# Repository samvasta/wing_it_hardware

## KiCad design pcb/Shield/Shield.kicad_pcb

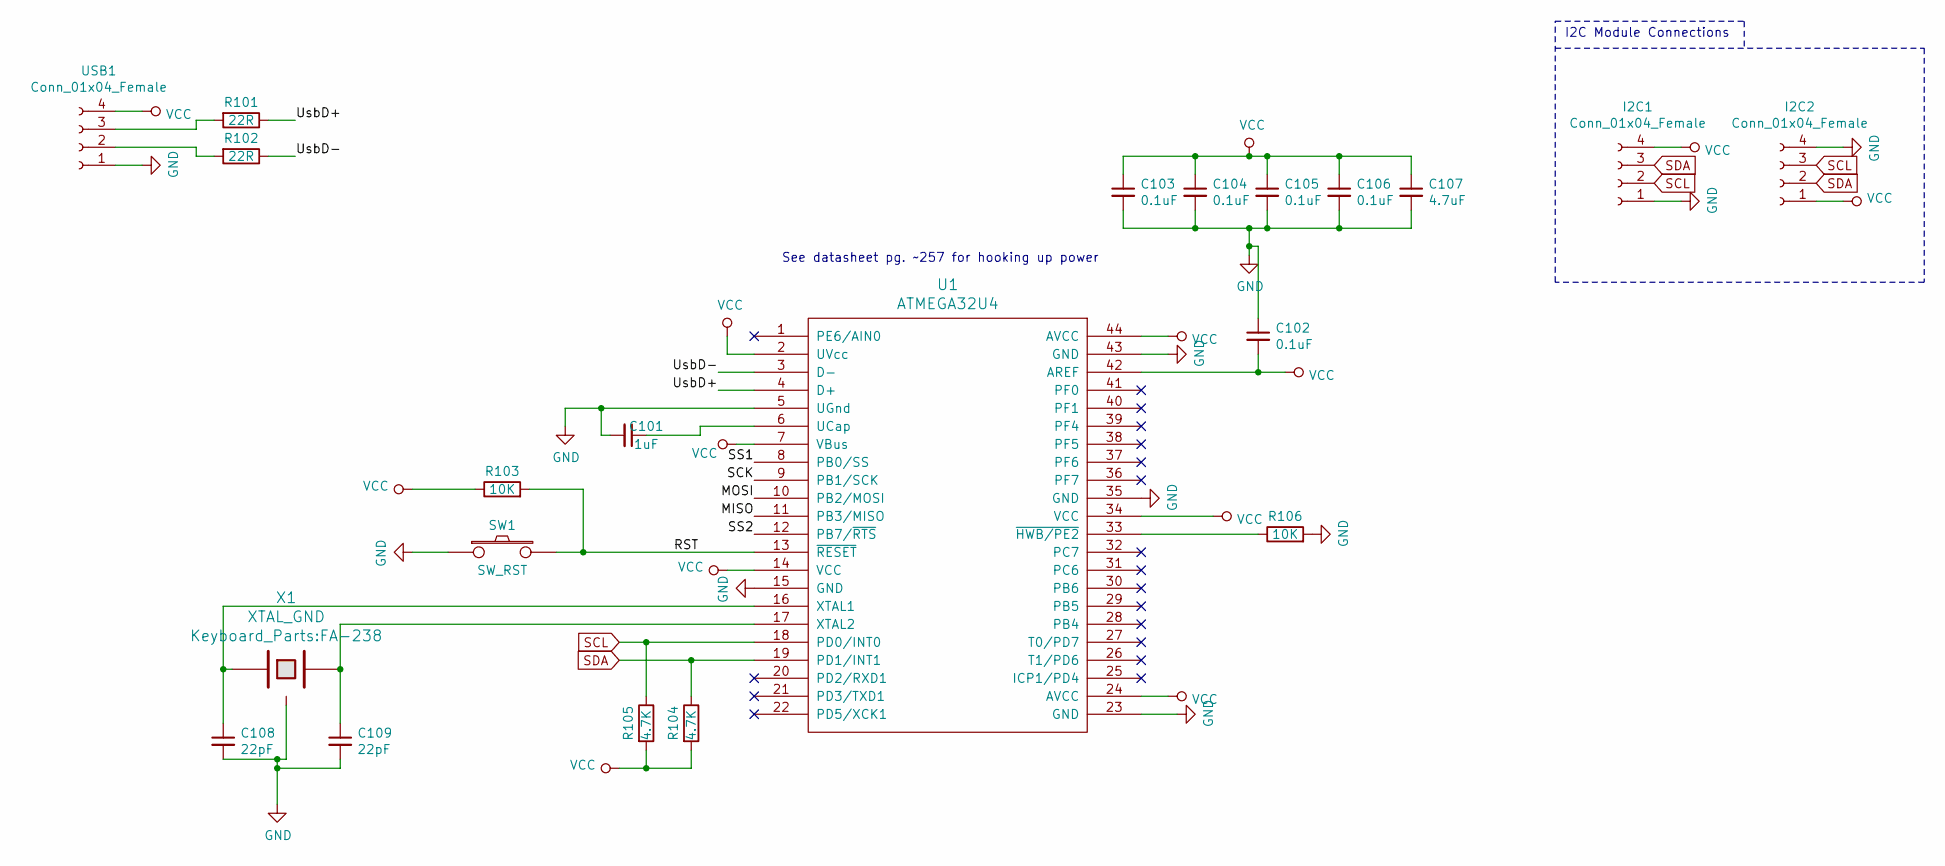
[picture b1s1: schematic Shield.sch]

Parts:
C101: 1uF; C_0805_2012Metric_Pad1.15x1.40mm_HandSolder
C102, C103, C104, C105, C106: 0.1uF; C_0805_2012Metric_Pad1.15x1.40mm_HandSolder
C107: 4.7uF; C_0805_2012Metric_Pad1.15x1.40mm_HandSolder
C108, C109: 22pF; C_0805_2012Metric_Pad1.15x1.40mm_HandSolder
I2C1, I2C2: Conn_01x04_Female; Terminal_Block_4pos_On_Shore_Tech.
R101, R102: 22R; R_0805_2012Metric_Pad1.15x1.40mm_HandSolder
R103, R106: 10K; R_0805_2012Metric_Pad1.15x1.40mm_HandSolder
R104, R105: 4.7K; R_0805_2012Metric_Pad1.15x1.40mm_HandSolder
SW1: SW_RST; MomentarySwitch_B3U-1000P
U1: ATMEGA32U4; ATMEGA32U4-AU_FixedMask
USB1: Conn_01x04_Female; Terminal_Block_4pos_On_Shore_Tech.
X1: XTAL_GND; FA-238

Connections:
/MISO: U1.11 (PB3/MISO)
/MOSI: U1.10 (PB2/MOSI)
/RST: R103.2, SW1.2, U1.13 (~RESET)
/SCK: U1.9 (PB1/SCK)
/SS1: U1.8 (PB0/SS)
/SS2: U1.12 (PB7/~RTS)
/UsbD+: R101.1, U1.4 (D+)
/UsbD-: R102.1, U1.3 (D-)
GND: C101.2, C102.1, C103.2, C104.2, C105.2, C106.2, C107.2, C108.2, C109.2, I2C1.1, I2C2.4, R106.2, SW1.1, U1.5 (UGnd), U1.15 (GND), U1.23 (GND), U1.35 (GND), U1.43 (GND), USB1.1, X1.3
unnamed: C101.1, U1.6 (UCap)
unnamed: C108.1, U1.16 (XTAL1), X1.1
unnamed: C109.1, U1.17 (XTAL2), X1.2
unnamed: R101.2, USB1.3
unnamed: R102.2, USB1.2
unnamed: R106.1, U1.33 (~HWB/PE2)
SCL: I2C1.2, I2C2.3, R105.1, U1.18 (PD0/INT0)
SDA: I2C1.3, I2C2.2, R104.1, U1.19 (PD1/INT1)
VCC: C102.2, C103.1, C104.1, C105.1, C106.1, C107.1, I2C1.4, I2C2.1, R103.1, R104.2, R105.2, U1.2 (UVcc), U1.7 (VBus), U1.14 (VCC), U1.24 (AVCC), U1.34 (VCC), U1.42 (AREF), U1.44 (AVCC), USB1.4

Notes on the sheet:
See datasheet pg. ~~257 for hooking up power
I2C Module Connections

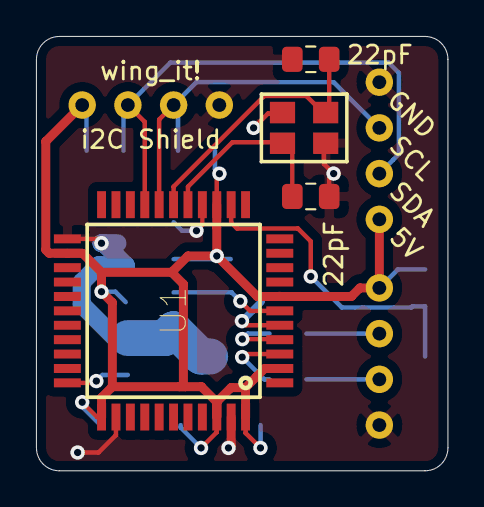
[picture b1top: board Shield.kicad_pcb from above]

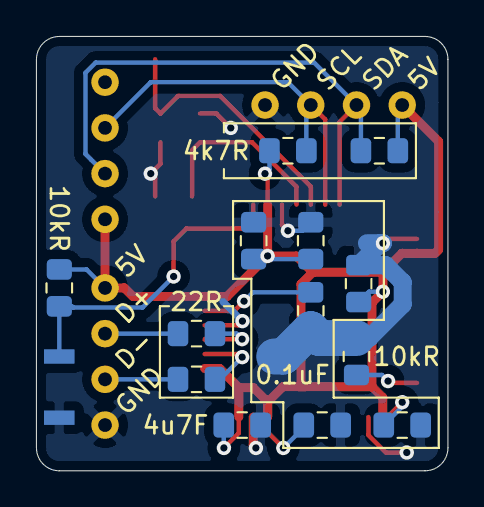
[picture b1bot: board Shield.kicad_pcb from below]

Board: 2 copper layers, 22.9 x 24.1 mm, 21 parts (15 on the bottom side), 13 nets.

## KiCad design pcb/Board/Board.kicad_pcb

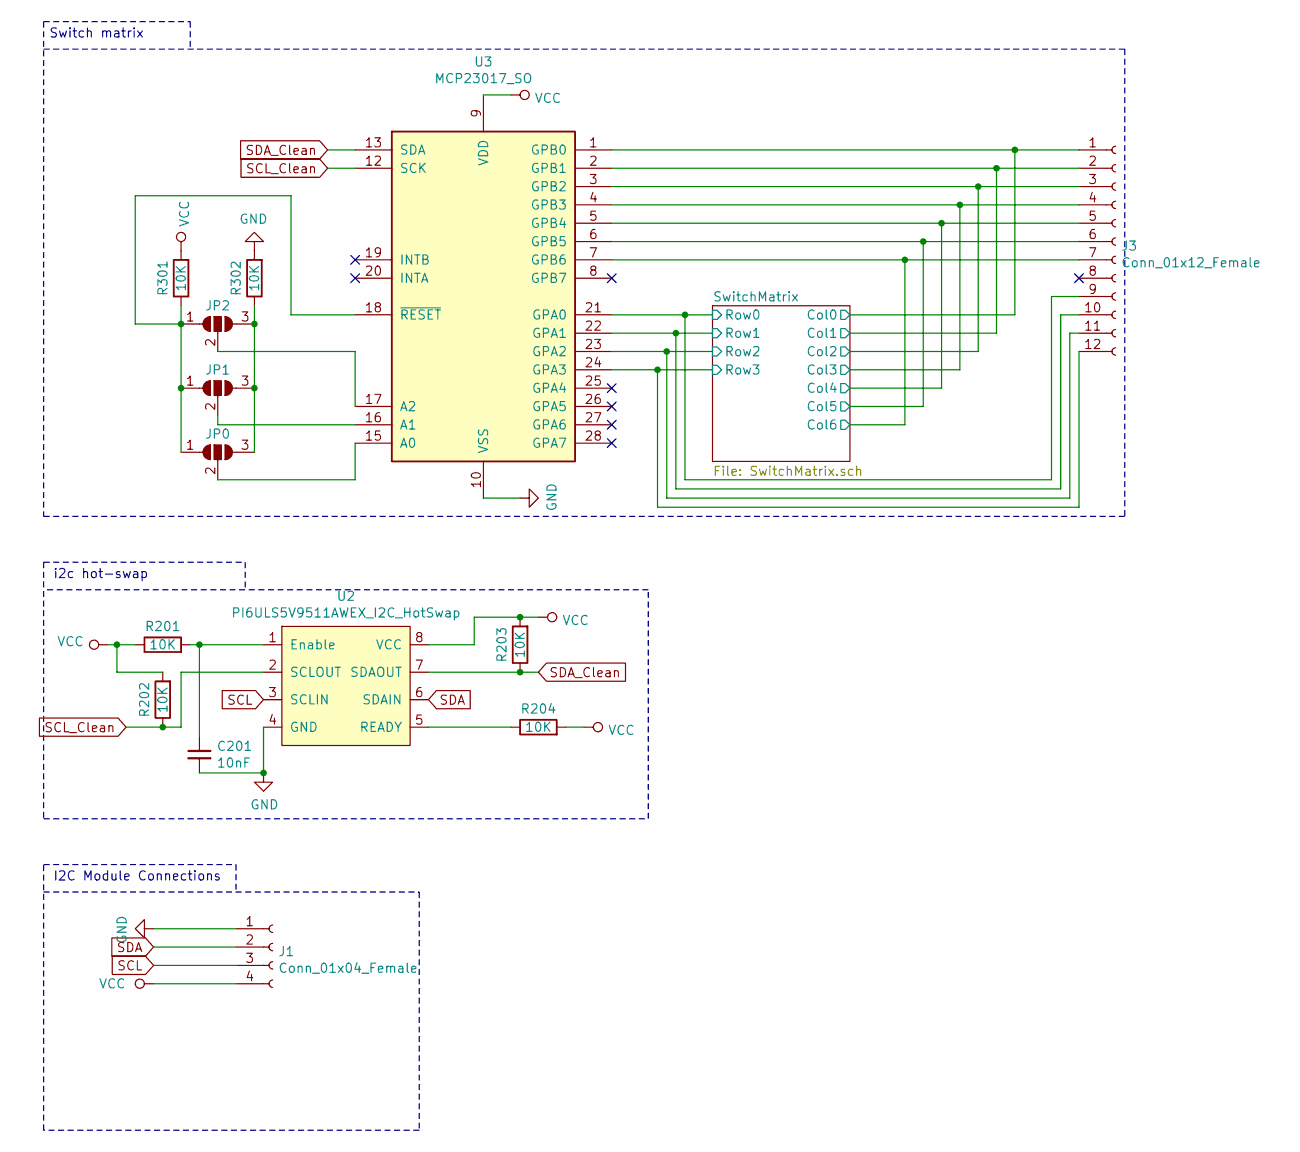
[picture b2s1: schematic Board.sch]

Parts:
C201: 10nF; C_0805_2012Metric_Pad1.15x1.40mm_HandSolder
J1: Conn_01x04_Female; PinHeader_1x04_P2.54mm_Vertical
J3: Conn_01x12_Female; PinHeader_1x12_P2.54mm_Vertical
JP0, JP1, JP2: SolderJumper_3_Open; SolderJumper-3_P1.3mm_Open_RoundedPad1.0x1.5mm
R201, R202, R203, R204, R301, R302: 10K; R_0805_2012Metric_Pad1.15x1.40mm_HandSolder
U2: PI6ULS5V9511AWEX_I2C_HotSwap; PI6ULS5V9511A_I2C_HotSwap
U3: MCP23017_SO; SSOP-28_5.3x10.2mm_P0.65mm

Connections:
/SwitchMatrix/Col0: J3.1, U3.1 (GPB0); also elsewhere on the board
/SwitchMatrix/Col1: J3.2, U3.2 (GPB1); also elsewhere on the board
/SwitchMatrix/Col2: J3.3, U3.3 (GPB2); also elsewhere on the board
/SwitchMatrix/Col3: J3.4, U3.4 (GPB3); also elsewhere on the board
/SwitchMatrix/Col4: J3.5, U3.5 (GPB4); also elsewhere on the board
/SwitchMatrix/Col5: J3.6, U3.6 (GPB5); also elsewhere on the board
/SwitchMatrix/Col6: J3.7, U3.7 (GPB6); also elsewhere on the board
/SwitchMatrix/Row0: J3.9, U3.21 (GPA0); also elsewhere on the board
/SwitchMatrix/Row1: J3.10, U3.22 (GPA1); also elsewhere on the board
/SwitchMatrix/Row2: J3.11, U3.23 (GPA2); also elsewhere on the board
/SwitchMatrix/Row3: J3.12, U3.24 (GPA3); also elsewhere on the board
GND: C201.2, J1.1, R302.2, U2.4 (GND), U3.10 (VSS); also elsewhere on the board
unnamed: C201.1, R201.2, U2.1 (Enable)
unnamed 40: JP0.1 (A), JP1.1 (A), JP2.1 (A), R301.1, U3.18 (~RESET~); also elsewhere on the board
unnamed 41: JP0.2 (C), U3.15 (A0); also elsewhere on the board
unnamed 42: JP0.3 (B), JP1.3 (B), JP2.3 (B), R302.1; also elsewhere on the board
unnamed 43: JP1.2 (C), U3.16 (A1); also elsewhere on the board
unnamed 44: JP2.2 (C), U3.17 (A2); also elsewhere on the board
unnamed: R204.1, U2.5 (READY)
unnamed 46: U3.8 (GPB7); also elsewhere on the board
unnamed 47: U3.11 (NC); also elsewhere on the board
unnamed 48: U3.14 (NC); also elsewhere on the board
unnamed 49: U3.19 (INTB); also elsewhere on the board
unnamed 50: U3.20 (INTA); also elsewhere on the board
unnamed 51: U3.25 (GPA4); also elsewhere on the board
unnamed 52: U3.26 (GPA5); also elsewhere on the board
unnamed 53: U3.27 (GPA6); also elsewhere on the board
unnamed 54: U3.28 (GPA7); also elsewhere on the board
SCL: J1.3, U2.3 (SCLIN)
SCL_Clean: R202.1, U2.2 (SCLOUT), U3.12 (SCK); also elsewhere on the board
SDA: J1.2, U2.6 (SDAIN)
SDA_Clean: R203.1, U2.7 (SDAOUT), U3.13 (SDA); also elsewhere on the board
VCC: J1.4, R201.1, R202.2, R203.2, R204.2, R301.2, U2.8 (VCC), U3.9 (VDD); also elsewhere on the board

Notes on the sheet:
Switch matrix
I2C Module Connections
i2c hot-swap

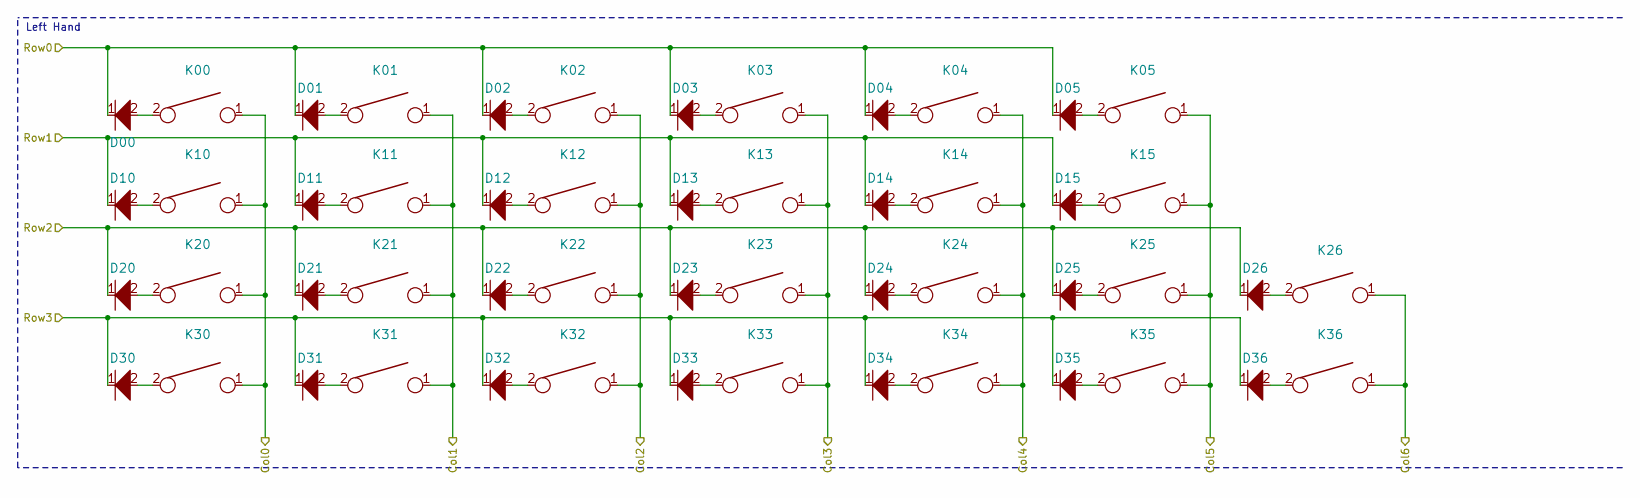
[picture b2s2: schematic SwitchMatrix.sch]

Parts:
D00, D01, D02, D03, D04, D05, D10, D11, D12, D13, D14, D15, D20, D21, D22, D23, D24, D25, D26, D30, D31, D32, D33, D34, D35, D36: D; D_MiniMELF_Handsoldering_Shorter_Pads_DoubleSided
K00, K01, K02, K03, K04, K05, K10, K11, K12, K13, K14, K15, K20, K21, K22, K23, K24, K25, K30, K31, K32, K33, K34, K35: KEYSW; Kailh_socket_reversible
K26, K36: KEYSW; switch_off_board

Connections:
/SwitchMatrix/Col0: K00.1, K10.1, K20.1, K30.1; also elsewhere on the board
/SwitchMatrix/Col1: K01.1, K11.1, K21.1, K31.1; also elsewhere on the board
/SwitchMatrix/Col2: K02.1, K12.1, K22.1, K32.1; also elsewhere on the board
/SwitchMatrix/Col3: K03.1, K13.1, K23.1, K33.1; also elsewhere on the board
/SwitchMatrix/Col4: K04.1, K14.1, K24.1, K34.1; also elsewhere on the board
/SwitchMatrix/Col5: K05.1, K15.1, K25.1, K35.1; also elsewhere on the board
/SwitchMatrix/Col6: K26.1, K36.1; also elsewhere on the board
/SwitchMatrix/Row0: D00.1, D01.1, D02.1, D03.1, D04.1, D05.1; also elsewhere on the board
/SwitchMatrix/Row1: D10.1, D11.1, D12.1, D13.1, D14.1, D15.1; also elsewhere on the board
/SwitchMatrix/Row2: D20.1, D21.1, D22.1, D23.1, D24.1, D25.1, D26.1; also elsewhere on the board
/SwitchMatrix/Row3: D30.1, D31.1, D32.1, D33.1, D34.1, D35.1, D36.1; also elsewhere on the board
unnamed: D00.2, K00.2
unnamed: D01.2, K01.2
unnamed: D02.2, K02.2
unnamed: D03.2, K03.2
unnamed: D04.2, K04.2
unnamed: D05.2, K05.2
unnamed: D10.2, K10.2
unnamed: D11.2, K11.2
unnamed: D12.2, K12.2
unnamed: D13.2, K13.2
unnamed: D14.2, K14.2
unnamed: D15.2, K15.2
unnamed: D20.2, K20.2
unnamed: D21.2, K21.2
unnamed: D22.2, K22.2
unnamed: D23.2, K23.2
unnamed: D24.2, K24.2
unnamed: D25.2, K25.2
unnamed: D26.2, K26.2
unnamed: D30.2, K30.2
unnamed: D31.2, K31.2
unnamed: D32.2, K32.2
unnamed: D33.2, K33.2
unnamed: D34.2, K34.2
unnamed: D35.2, K35.2
unnamed: D36.2, K36.2

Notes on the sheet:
Left Hand

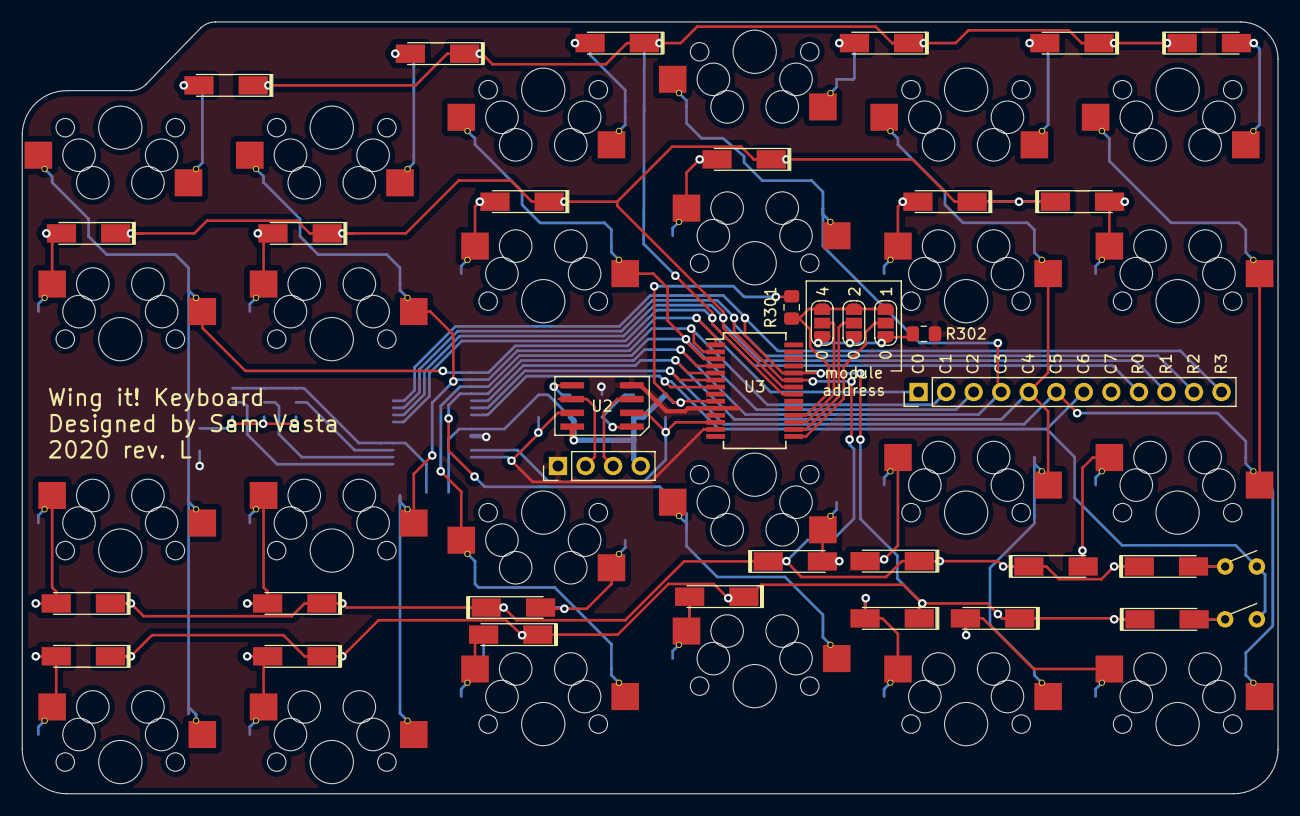
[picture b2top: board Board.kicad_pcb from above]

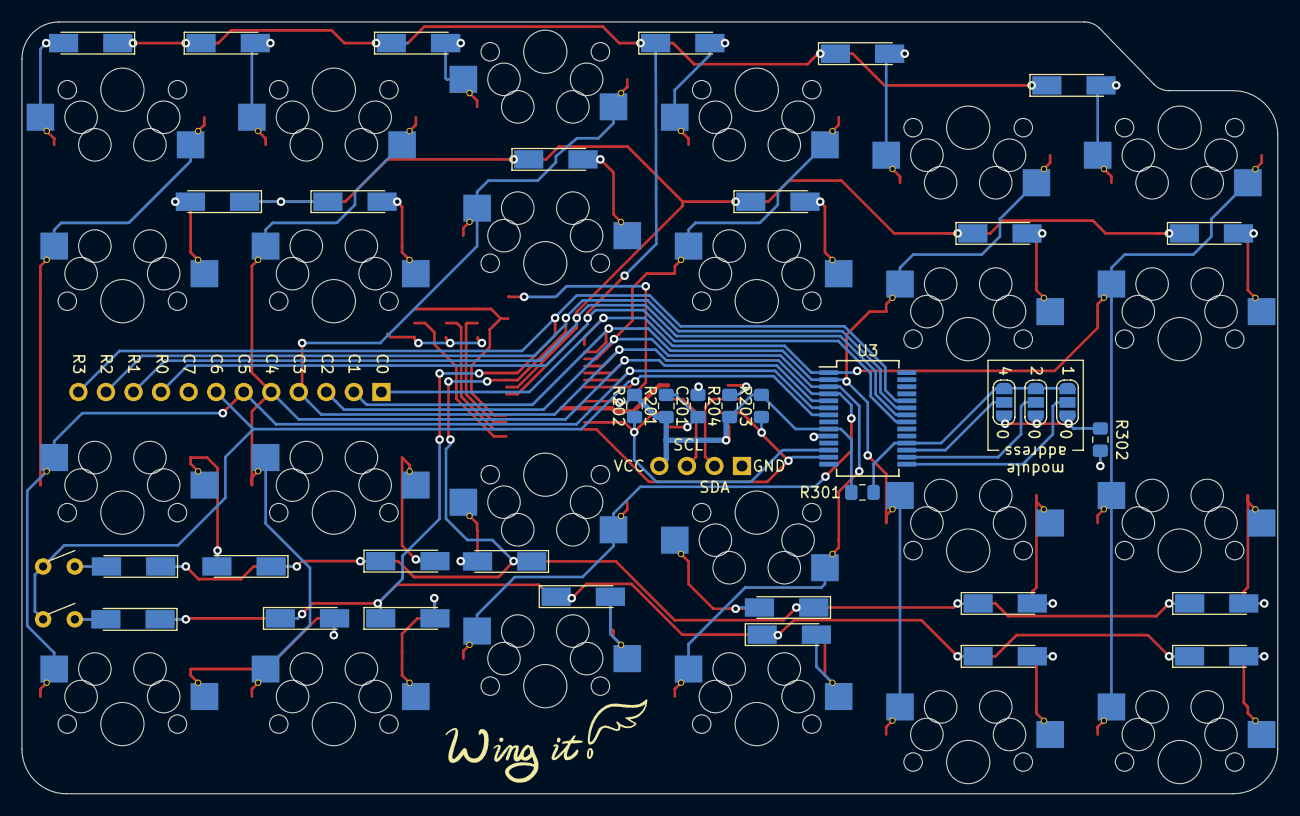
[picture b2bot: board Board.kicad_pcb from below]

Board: 2 copper layers, 115.8 x 71.1 mm, 72 parts (11 on the bottom side), 59 nets.

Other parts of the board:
JP0#2, JP1#2, JP2#2: SolderJumper_3_Open; SolderJumper-3_P1.3mm_Open_RoundedPad1.0x1.5mm
R301#2, R302#2: 10K; R_0805_2012Metric_Pad1.15x1.40mm_HandSolder
U3#2: MCP23017_SO; SSOP-28_5.3x10.2mm_P0.65mm

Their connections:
/SwitchMatrix/Col0: U3#2.1; also elsewhere on the board
/SwitchMatrix/Col1: U3#2.2; also elsewhere on the board
/SwitchMatrix/Col2: U3#2.3; also elsewhere on the board
/SwitchMatrix/Col3: U3#2.4; also elsewhere on the board
/SwitchMatrix/Col4: U3#2.5; also elsewhere on the board
/SwitchMatrix/Col5: U3#2.6; also elsewhere on the board
/SwitchMatrix/Col6: U3#2.7; also elsewhere on the board
/SwitchMatrix/Row0: U3#2.21; also elsewhere on the board
/SwitchMatrix/Row1: U3#2.22; also elsewhere on the board
/SwitchMatrix/Row2: U3#2.23; also elsewhere on the board
/SwitchMatrix/Row3: U3#2.24; also elsewhere on the board
GND: R302#2.2, U3#2.10; also elsewhere on the board
unnamed 40: JP0#2.1, JP1#2.1, JP2#2.1, R301#2.1, U3#2.18; also elsewhere on the board
unnamed 41: JP0#2.2, U3#2.15; also elsewhere on the board
unnamed 42: JP0#2.3, JP1#2.3, JP2#2.3, R302#2.1; also elsewhere on the board
unnamed 43: JP1#2.2, U3#2.16; also elsewhere on the board
unnamed 44: JP2#2.2, U3#2.17; also elsewhere on the board
unnamed 46: U3#2.8; also elsewhere on the board
unnamed 47: U3#2.11; also elsewhere on the board
unnamed 48: U3#2.14; also elsewhere on the board
unnamed 49: U3#2.19; also elsewhere on the board
unnamed 50: U3#2.20; also elsewhere on the board
unnamed 51: U3#2.25; also elsewhere on the board
unnamed 52: U3#2.26; also elsewhere on the board
unnamed 53: U3#2.27; also elsewhere on the board
unnamed 54: U3#2.28; also elsewhere on the board
SCL_Clean: U3#2.12; also elsewhere on the board
SDA_Clean: U3#2.13; also elsewhere on the board
VCC: R301#2.2, U3#2.9; also elsewhere on the board

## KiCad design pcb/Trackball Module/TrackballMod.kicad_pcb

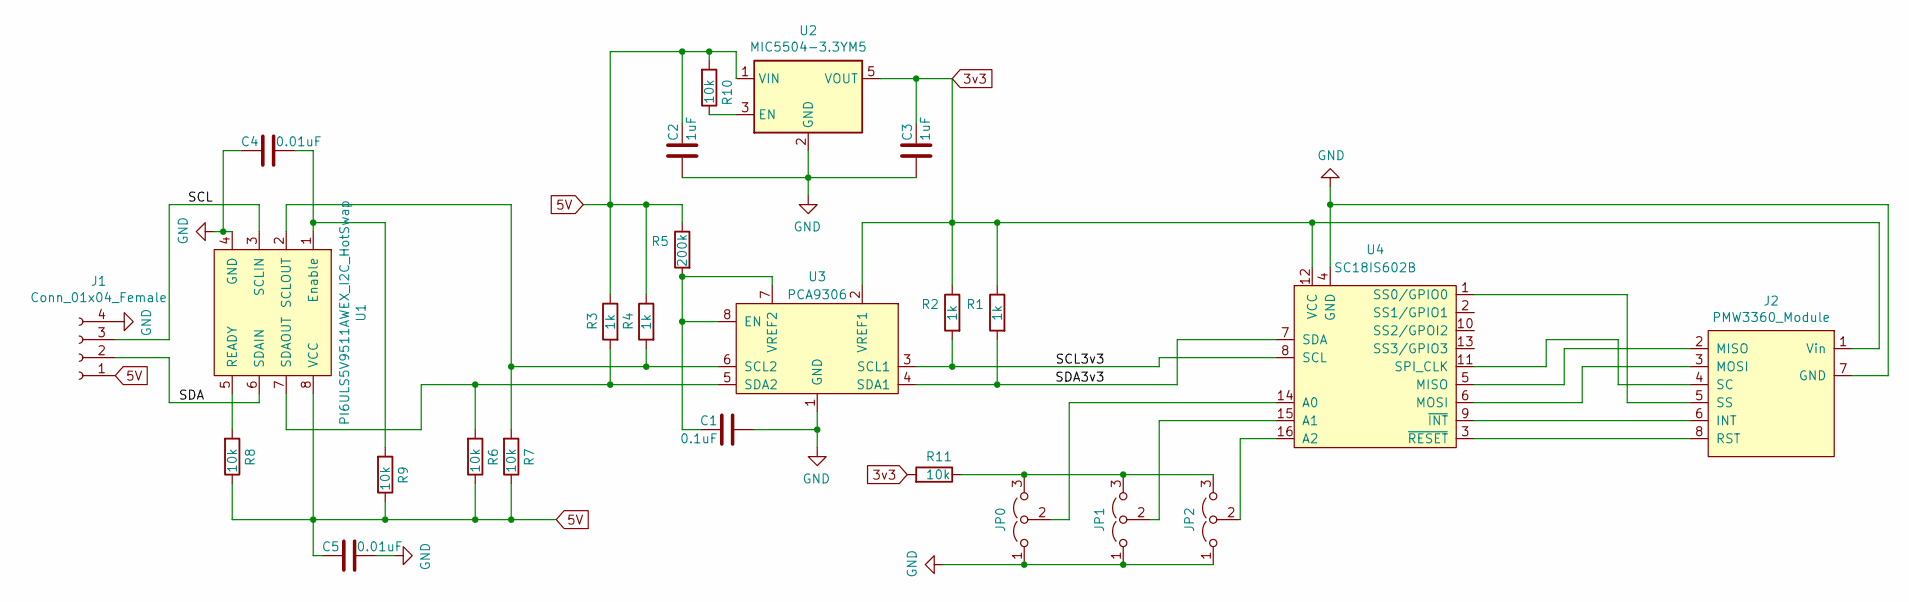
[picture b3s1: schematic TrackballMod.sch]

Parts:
C1: 0.1uF; C_0805_2012Metric_Pad1.15x1.40mm_HandSolder
C2, C3: 1uF; C_0805_2012Metric_Pad1.15x1.40mm_HandSolder
C4, C5: 0.01uF; C_0805_2012Metric_Pad1.15x1.40mm_HandSolder
J1: Conn_01x04_Female; PinSocket_1x04_P2.54mm_Vertical
J2: PMW3360_Module; PinHeader_1x08_P2.54mm_Vertical
JP0, JP1, JP2: Jumper_3_Open; SolderJumper-3_P1.3mm_Open_RoundedPad1.0x1.5mm
R1, R2, R3, R4: 1k; R_0805_2012Metric_Pad1.15x1.40mm_HandSolder
R5: 200k; R_0805_2012Metric_Pad1.15x1.40mm_HandSolder
R6, R7, R8, R9, R10, R11: 10k; R_0805_2012Metric_Pad1.15x1.40mm_HandSolder
U1: PI6ULS5V9511AWEX_I2C_HotSwap; PI6ULS5V9511A_I2C_HotSwap
U2: MIC5504-3.3YM5; SOT-23-5
U3: PCA9306; TI_PCA9306
U4: SC18IS602B; NXP_SC18IS602B

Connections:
3v3: C3.1, J2.1 (Vin), R1.1, R2.1, R11.2, U2.5 (VOUT), U3.2 (VREF1), U4.12 (VCC)
5V: C2.1, C5.1, J1.1, R3.1, R4.1, R5.1, R6.1, R7.1, R8.1, R9.1, R10.2, U1.8 (VCC), U2.1 (VIN)
/SCL: J1.3, U1.3 (SCLIN)
/SCL3v3: R2.2, U3.3 (SCL1), U4.8 (SCL)
/SDA: J1.2, U1.6 (SDAIN)
/SDA3v3: R1.2, U3.4 (SDA1), U4.7 (SDA)
GND: C1.2, C2.2, C3.2, C4.1, C5.2, J1.4, J2.7 (GND), JP0.1 (A), JP1.1 (A), JP2.1 (A), U1.4 (GND), U2.2 (GND), U3.1 (GND), U4.4 (GND)
unnamed: C1.1, R5.2, U3.7 (VREF2), U3.8 (EN)
unnamed: C4.2, R9.2, U1.1 (Enable)
unnamed: J2.2 (MISO), U4.5 (MISO)
unnamed: J2.3 (MOSI), U4.6 (MOSI)
unnamed: J2.4 (SC), U4.11 (SPI_CLK)
unnamed: J2.5 (SS), U4.1 (SS0/GPIO0)
unnamed: J2.6 (INT), U4.9 (~INT)
unnamed: J2.8 (RST), U4.3 (~RESET)
unnamed: JP0.2 (C), U4.14 (A0)
unnamed: JP0.3 (B), JP1.3 (B), JP2.3 (B), R11.1
unnamed: JP1.2 (C), U4.15 (A1)
unnamed: JP2.2 (C), U4.16 (A2)
unnamed: R3.2, R6.2, U1.7 (SDAOUT), U3.5 (SDA2)
unnamed: R4.2, R7.2, U1.2 (SCLOUT), U3.6 (SCL2)
unnamed: R8.2, U1.5 (READY)
unnamed: R10.1, U2.3 (EN)

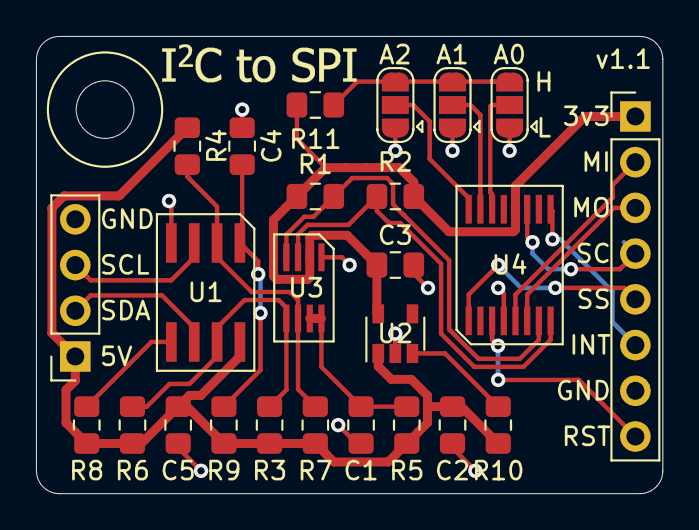
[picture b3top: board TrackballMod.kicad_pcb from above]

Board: 2 copper layers, 34.8 x 25.4 mm, 25 parts (0 on the bottom side), 23 nets.

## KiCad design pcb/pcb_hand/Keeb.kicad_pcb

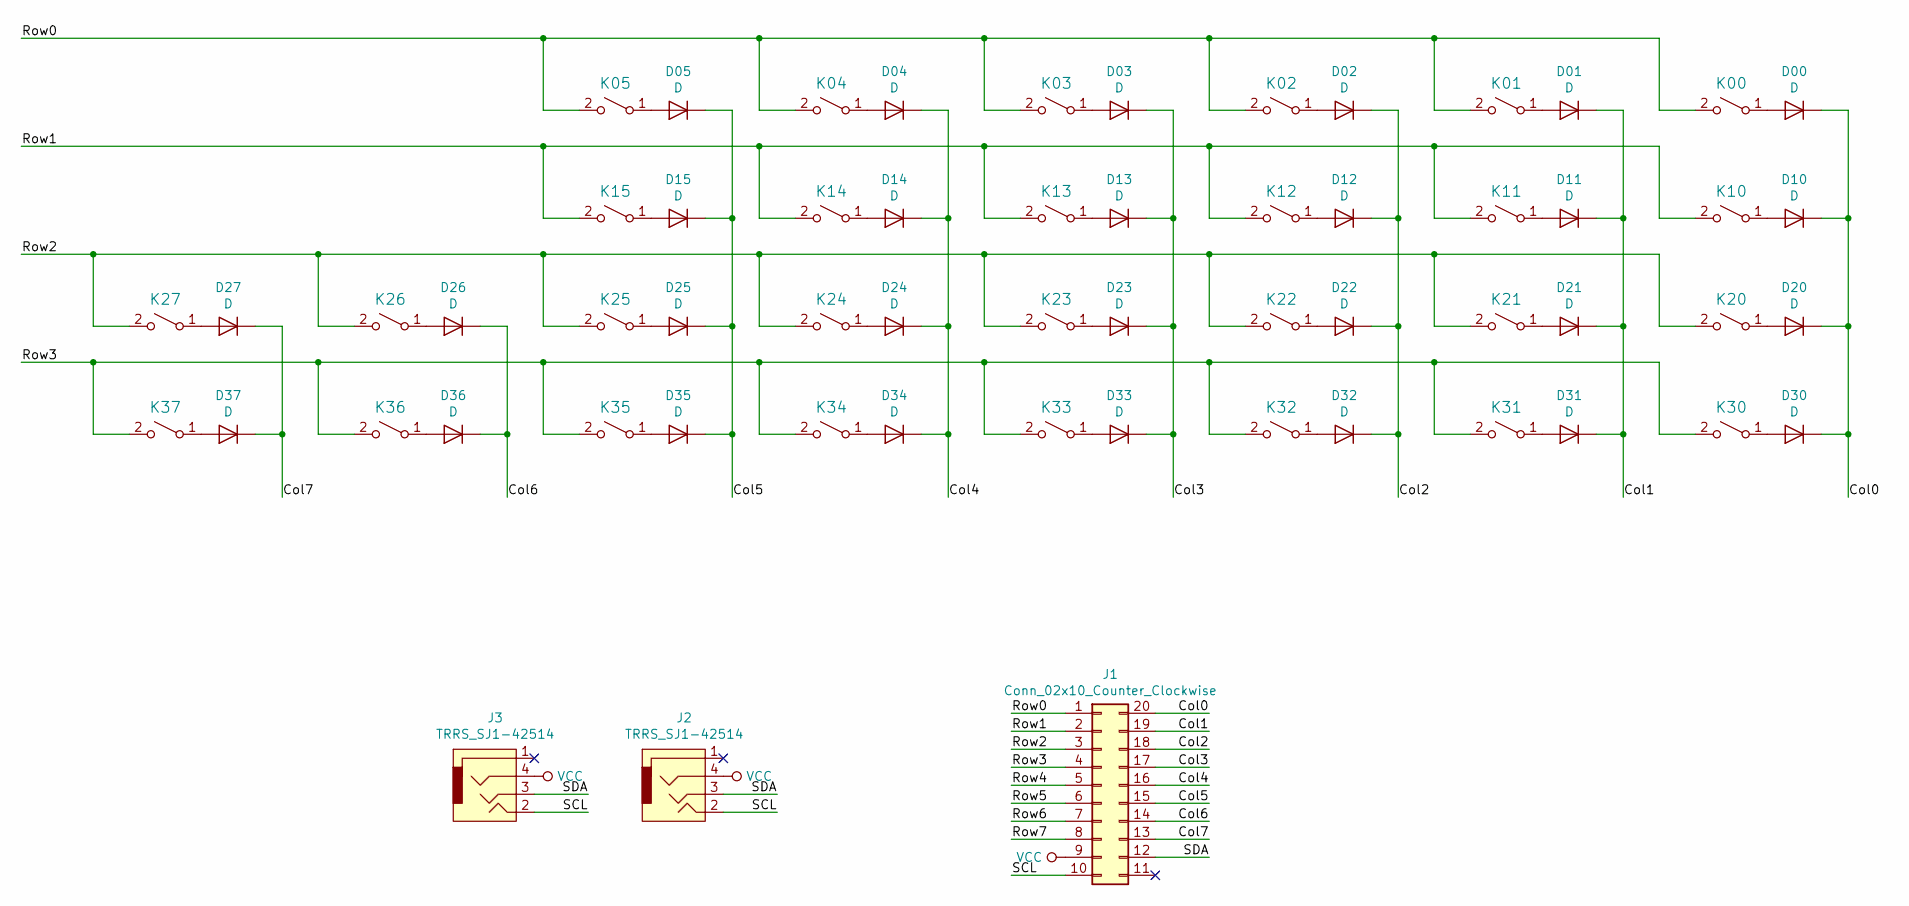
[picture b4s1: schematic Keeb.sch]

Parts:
D00, D01, D02, D03, D04, D05, D10, D11, D12, D13, D14, D15, D20, D21, D22, D23, D24, D25, D26, D27, D30, D31, D32, D33, D34, D35, D36, D37: D; D_MiniMELF_Handsoldering_Shorter_Pads_DoubleSided
J1: Conn_02x10_Counter_Clockwise; Backplane_Connector_Hirose_PCN_20pos_Receptacle
J2, J3: TRRS_SJ1-42514; 3.5mm_Cut_out
K00, K01, K02, K03, K04, K05, K10, K11, K12, K13, K14, K15, K20, K21, K22, K23, K24, K25, K26, K27, K30, K31, K32, K33, K34, K35, K36, K37: KEYSW; Kailh_socket_reversible

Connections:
/Col0: D00.1 (K), D10.1 (K), D20.1 (K), D30.1 (K), J1.20
/Col1: D01.1 (K), D11.1 (K), D21.1 (K), D31.1 (K), J1.19
/Col2: D02.1 (K), D12.1 (K), D22.1 (K), D32.1 (K), J1.18
/Col3: D03.1 (K), D13.1 (K), D23.1 (K), D33.1 (K), J1.17
/Col4: D04.1 (K), D14.1 (K), D24.1 (K), D34.1 (K), J1.16
/Col5: D05.1 (K), D15.1 (K), D25.1 (K), D35.1 (K), J1.15
/Col6: D26.1 (K), D36.1 (K), J1.14
/Col7: D27.1 (K), D37.1 (K), J1.13
/Row0: J1.1, K00.2 (B), K01.2 (B), K02.2 (B), K03.2 (B), K04.2 (B), K05.2 (B)
/Row1: J1.2, K10.2 (B), K11.2 (B), K12.2 (B), K13.2 (B), K14.2 (B), K15.2 (B)
/Row2: J1.3, K20.2 (B), K21.2 (B), K22.2 (B), K23.2 (B), K24.2 (B), K25.2 (B), K26.2 (B), K27.2 (B)
/Row3: J1.4, K30.2 (B), K31.2 (B), K32.2 (B), K33.2 (B), K34.2 (B), K35.2 (B), K36.2 (B), K37.2 (B)
/Row4: J1.5
/Row5: J1.6
/Row6: J1.7
/Row7: J1.8
/SCL: J1.10, J2.2, J3.2
/SDA: J1.12, J2.3, J3.3
unnamed: D00.2 (A), K00.1 (A)
unnamed: D01.2 (A), K01.1 (A)
unnamed: D02.2 (A), K02.1 (A)
unnamed: D03.2 (A), K03.1 (A)
unnamed: D04.2 (A), K04.1 (A)
unnamed: D05.2 (A), K05.1 (A)
unnamed: D10.2 (A), K10.1 (A)
unnamed: D11.2 (A), K11.1 (A)
unnamed: D12.2 (A), K12.1 (A)
unnamed: D13.2 (A), K13.1 (A)
unnamed: D14.2 (A), K14.1 (A)
unnamed: D15.2 (A), K15.1 (A)
unnamed: D20.2 (A), K20.1 (A)
unnamed: D21.2 (A), K21.1 (A)
unnamed: D22.2 (A), K22.1 (A)
unnamed: D23.2 (A), K23.1 (A)
unnamed: D24.2 (A), K24.1 (A)
unnamed: D25.2 (A), K25.1 (A)
unnamed: D26.2 (A), K26.1 (A)
unnamed: D27.2 (A), K27.1 (A)
unnamed: D30.2 (A), K30.1 (A)
unnamed: D31.2 (A), K31.1 (A)
unnamed: D32.2 (A), K32.1 (A)
unnamed: D33.2 (A), K33.1 (A)
unnamed: D34.2 (A), K34.1 (A)
unnamed: D35.2 (A), K35.1 (A)
unnamed: D36.2 (A), K36.1 (A)
unnamed: D37.2 (A), K37.1 (A)
VCC: J1.9, J2.4, J3.4

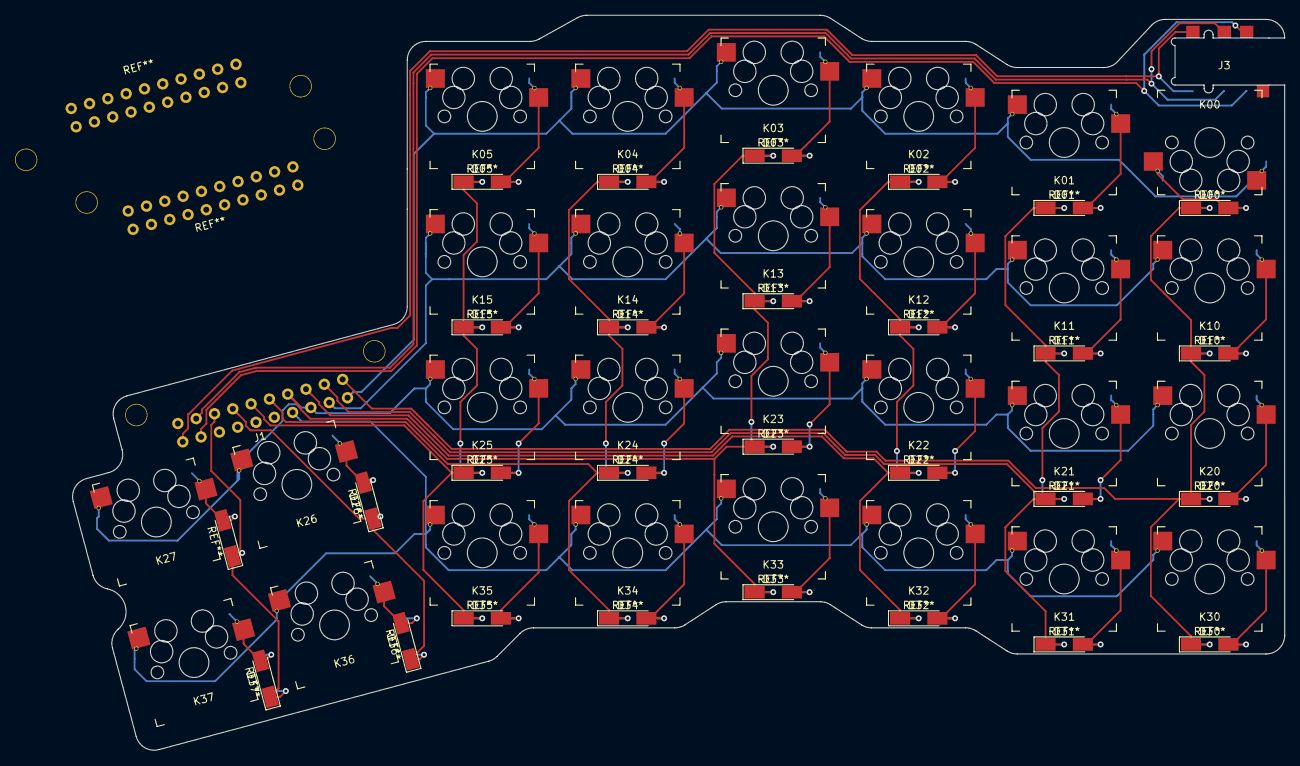
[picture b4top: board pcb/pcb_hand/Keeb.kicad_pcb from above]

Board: 2 copper layers, 162.5 x 98.5 mm, 59 parts (1 on the bottom side), 43 nets.
